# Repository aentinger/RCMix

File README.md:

💾 RC Mixer
===========

The LXRobotics P20 RC Mixer is a device which can mix up to 4 standard RC PWM inputs (pulse period 20 ms, pulse duration 1-2 ms) to up to 6 standard RC PWM outputs applying any used definable control algorithm.

# 📸 Image

## 💻 Installation

* Install the Arduino IDE

```
sudo apt-get install arduino
```
* Clone this repository

```
git clone https://github.com/aentinger/rcmix
```

## 💻 Building

* Open project in Arduino IDE by left clicking on `rcmixarduino.ino`

* Select ATMega32U4 MCU via the menu `Tools - Board - Arduino Leonardo`

* Compile with `Ctrl+R`

## 💻 Upload

* Connect an **AVR ISP mkII** with the rcmix hardware
 
* After successful compilation of the Arduino sketch select `Tools - Programmer - AVRISP mkII`
 
* Upload with `Ctrl+U`

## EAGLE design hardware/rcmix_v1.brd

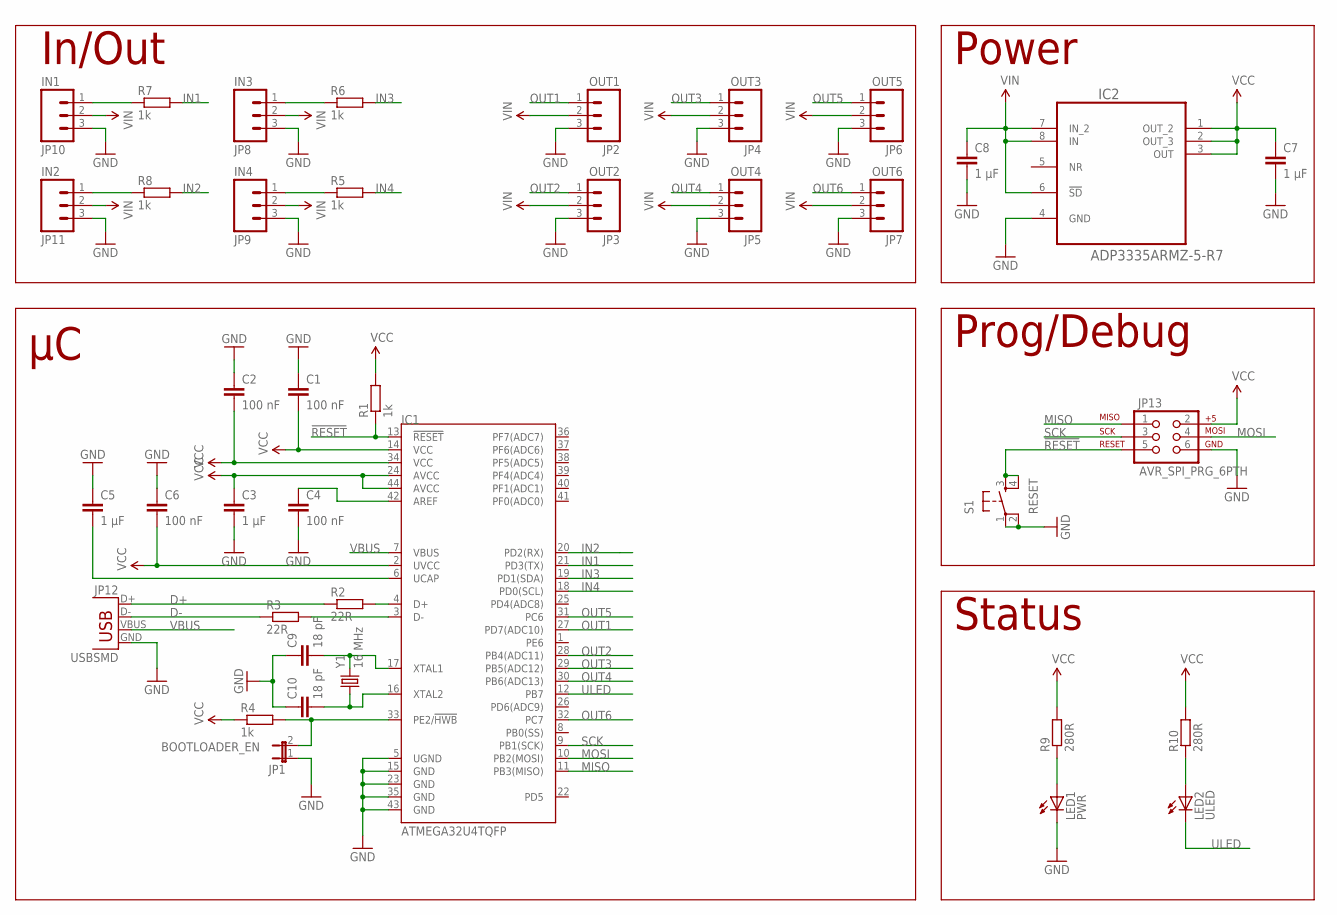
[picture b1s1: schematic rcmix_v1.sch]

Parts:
C1, C2, C4, C6: 100 nF; C0603K
C3, C5, C7, C8: 1 µF; C0603K
C9, C10: 18 pF; C0603K
IC1: ATMEGA32U4TQFP; SPARKFUN-DIGITALIC_TQFP44
IC2: ADP3335ARMZ-5-R7; SOP65P490X110-8N
JP1: BOOTLOADER_EN; JP1
JP2: OUT1; 1X03
JP3: OUT2; 1X03
JP4: OUT3; 1X03
JP5: OUT4; 1X03
JP6: OUT5; 1X03
JP7: OUT6; 1X03
JP8: IN3; 1X03
JP9: IN4; 1X03
JP10: IN1; 1X03
JP11: IN2; 1X03
JP12: USBSMD; USB-MINIB
JP13: AVR_SPI_PRG_6PTH; 2X3
LED1: PWR; CHIP-LED0603
LED2: ULED; CHIP-LED0603
R1, R4, R5, R6, R7, R8: 1k; R0603
R2, R3: 22R; R0603
R9, R10: 280R; R0603
S1: RESET; TACTILE-PTH
Y1: 16 MHz; CRYSTAL-TXC-7A

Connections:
!RESET: IC1.13 (!RESET), JP13.5, R1.1, S1.3, S1.4
D+: JP12.D+, R2.1
D-: JP12.D-, R3.1
GND: C1.1, C2.1, C3.2, C4.2, C5.1, C6.1, C7.2, C8.2, C9.1, C10.1, IC1.5 (UGND), IC1.15 (GND), IC1.23 (GND), IC1.35 (GND), IC1.43 (GND), IC2.4 (GND), JP1.1, JP2.3, JP3.3, JP4.3, JP5.3, JP6.3, JP7.3, JP8.3, JP9.3, JP10.3, JP11.3, JP12.GND, JP13.6, LED1.C, S1.1, S1.2
IN1: IC1.21 (PD3(TX)), R7.2
IN2: IC1.20 (PD2(RX)), R8.2
IN3: IC1.19 (PD1(SDA)), R6.2
IN4: IC1.18 (PD0(SCL)), R5.2
MISO: IC1.11 (PB3(MISO)), JP13.1
MOSI: IC1.10 (PB2(MOSI)), JP13.4
unnamed: IC1.4 (D+), R2.2
unnamed: IC1.3 (D-), R3.2
unnamed: C4.1, IC1.42 (AREF)
unnamed: C5.2, IC1.6 (UCAP)
unnamed: IC1.33 (PE2/!HWB), JP1.2, R4.2
unnamed: JP10.1, R7.1
unnamed: JP11.1, R8.1
unnamed: JP8.1, R6.1
unnamed: JP9.1, R5.1
unnamed: C9.2, IC1.17 (XTAL1), Y1.P$2 (2)
unnamed: LED1.A, R9.1
unnamed: C10.2, IC1.16 (XTAL2), Y1.P$1 (1)
unnamed: LED2.A, R10.1
OUT1: IC1.27 (PD7(ADC10)), JP2.1
OUT2: IC1.28 (PB4(ADC11)), JP3.1
OUT3: IC1.29 (PB5(ADC12)), JP4.1
OUT4: IC1.30 (PB6(ADC13)), JP5.1
OUT5: IC1.31 (PC6), JP6.1
OUT6: IC1.32 (PC7), JP7.1
SCK: IC1.9 (PB1(SCK)), JP13.3
ULED: IC1.12 (PB7), LED2.C
VBUS: IC1.7 (VBUS), JP12.VBUS
VCC: C1.2, C2.2, C3.1, C6.2, C7.1, IC1.2 (UVCC), IC1.14 (VCC), IC1.24 (AVCC), IC1.34 (VCC), IC1.44 (AVCC), IC2.1 (OUT_2), IC2.2 (OUT_3), IC2.3 (OUT), JP13.2, R1.2, R4.1, R9.2, R10.2
VIN: C8.1, IC2.6 (!SD), IC2.7 (IN_2), IC2.8 (IN), JP2.2, JP3.2, JP4.2, JP5.2, JP6.2, JP7.2, JP8.2, JP9.2, JP10.2, JP11.2

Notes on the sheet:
In/Out
Power
Prog/Debug
Status

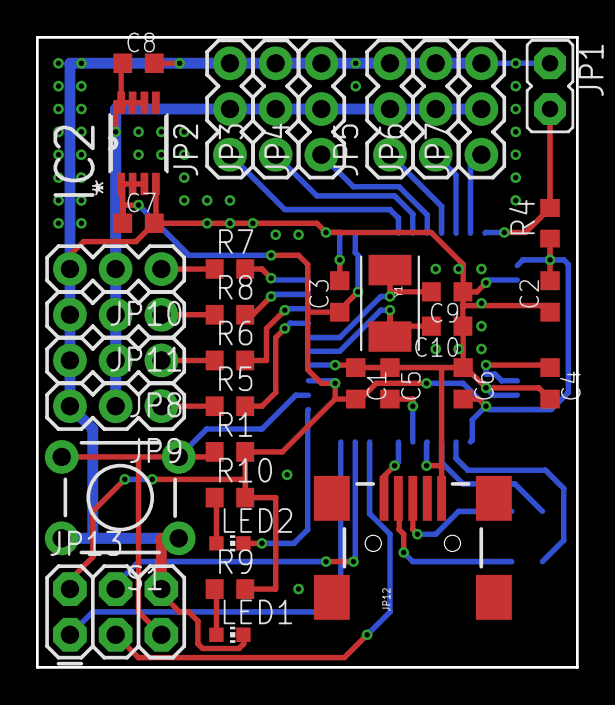
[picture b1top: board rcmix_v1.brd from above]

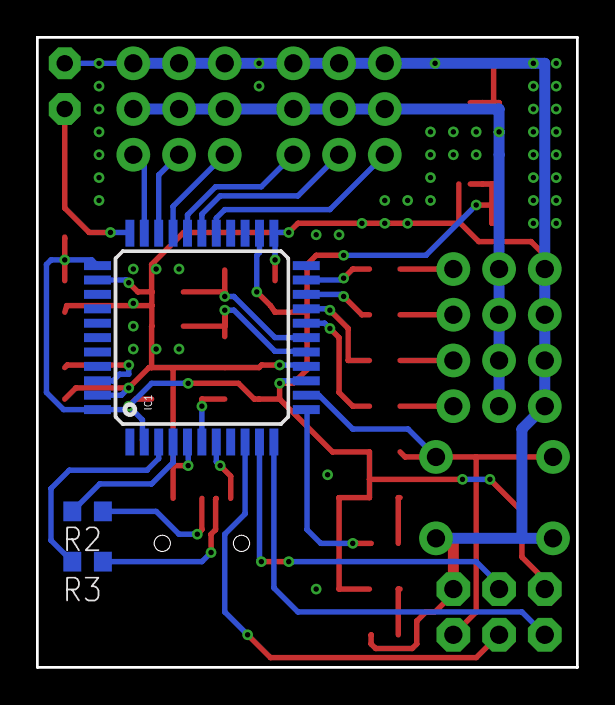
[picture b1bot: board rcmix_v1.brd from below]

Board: 2 copper layers, 30.0 x 35.0 mm, 39 parts (3 on the bottom side), 34 nets.

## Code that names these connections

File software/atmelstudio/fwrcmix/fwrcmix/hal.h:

/**
 * \file hal.h
 * \author Alexander Entinger, MSc
 * \copyright LXRobotics GmbH
 * \brief hardware abstraction layer
 * \license 
 */

#ifndef HAL_H_
#define HAL_H_

/************************************************************************/
/* INCLUDES                                                             */
/************************************************************************/

#include <avr/io.h>

/************************************************************************/
/* DEFINES                                                              */
/************************************************************************/

/* OUT1 = PD7 */

#define OUT1_DDR		(DDRD)
#define OUT1_PORT		(PORTD)
#define OUT1_bm			(1<<7)

/* OUT2 = PB4 */

#define OUT2_DDR		(DDRB)
#define OUT2_PORT		(PORTB)
#define OUT2_bm			(1<<4)

/* OUT3 = PB5 */

#define OUT3_DDR		(DDRB)
#define OUT3_PORT		(PORTB)
#define OUT3_bm			(1<<5)

/* OUT4 = PB6 */

#define OUT4_DDR		(DDRB)
#define OUT4_PORT		(PORTB)
#define OUT4_bm			(1<<6)

/* OUT5 = PC6 */

#define OUT5_DDR		(DDRC)
#define OUT5_PORT		(PORTC)
#define OUT5_bm			(1<<6)

/* OUT6 = PC7 */

#define OUT6_DDR		(DDRC)
#define OUT6_PORT		(PORTC)
#define OUT6_bm			(1<<7)

/* ULED = PB7 */

#define ULED_DDR		(DDRB)
#define ULED_PORT		(PORTB)
#define ULED_bm			(1<<7)

/* IN1 = PD3 = INT3 */

#define IN1_DDR				(DDRD)
#define IN1_PORT			(PORTD)
#define IN1_bm				(1<<3)
#define EINT_IN1_rising_bm	((1<<ISC31) | (1<<ISC30))
#define EINT_IN1_falling_bm	(1<<ISC31)
#define EINT_IN1_clear_bm	(~EINT_IN1_rising_bm)

/* IN2 = PD2 = INT2 */

#define IN2_DDR				(DDRD)
#define IN2_PORT			(PORTD)
#define IN2_bm				(1<<2)
#define EINT_IN2_rising_bm	((1<<ISC21) | (1<<ISC20))
#define EINT_IN2_falling_bm	(1<<ISC21)
#define EINT_IN2_clear_bm	(~EINT_IN2_rising_bm)

/* IN3 = PD1 = INT1 */

#define IN3_DDR				(DDRD)
#define IN3_PORT			(PORTD)
#define IN3_bm				(1<<1)
#define EINT_IN3_rising_bm	((1<<ISC11) | (1<<ISC10))
#define EINT_IN3_falling_bm	(1<<ISC11)
#define EINT_IN3_clear_bm	(~EINT_IN3_rising_bm)

/* IN4 = PD0 = INT0 */

#define IN4_DDR				(DDRD)
#define IN4_PORT			(PORTD)
#define IN4_bm				(1<<0)
#define EINT_IN4_rising_bm	((1<<ISC01) | (1<<ISC00))
#define EINT_IN4_falling_bm	(1<<ISC01)
#define EINT_IN4_clear_bm	(~EINT_IN4_rising_bm)

/************************************************************************/
/* PUBLIC PROTOTYPES                                                    */
/************************************************************************/

void initOut1();
void setOut1();
void clearOut1();
	
void initOut2();
void setOut2();
void clearOut2();

void initOut3();
void setOut3();
void clearOut3();
	
void initOut4();
void setOut4();
void clearOut4();
	
void initOut5();
void setOut5();
void clearOut5();
	
void initOut6();
void setOut6();
void clearOut6();

void initULed();
void setULed();
void clearULed();
	
void initIn1();
void triggerIn1AtRisingEdge();
void triggerIn1AtFallingEdge();

void initIn2();
void triggerIn2AtRisingEdge();
void triggerIn2AtFallingEdge();

void initIn3();
void triggerIn3AtRisingEdge();
void triggerIn3AtFallingEdge();

void initIn4();
void triggerIn4AtRisingEdge();
void triggerIn4AtFallingEdge();

#endif /* HAL_H_ */

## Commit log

2015-12-31 Adding initial commit of firmware for rc mix
2016-01-08 Basic software architecture inclusive one demo project complete
2016-01-08 Bugfix in functionality for transitioning between failsafe and mixing state
2016-01-26 Adding control algorithm for omnidirectional driving
2016-05-13 Transforming atmel studio code to arduino code
2017-06-27 Adding hardware + images
2017-06-27 Removing license file
2025-03-26 Add BOM.
2025-03-26 Pretty up README.

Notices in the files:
parts and their libraries:
SparkFun-DigitalIC: Licensing: CC v3.0 Share-Alike You are welcome to use this library for commercial purposes.
SparkFun-FreqCtrl: Licensing: Creative Commons ShareAlike 4.0 International - https://creativecommons.org/licenses/by-sa/4.0
